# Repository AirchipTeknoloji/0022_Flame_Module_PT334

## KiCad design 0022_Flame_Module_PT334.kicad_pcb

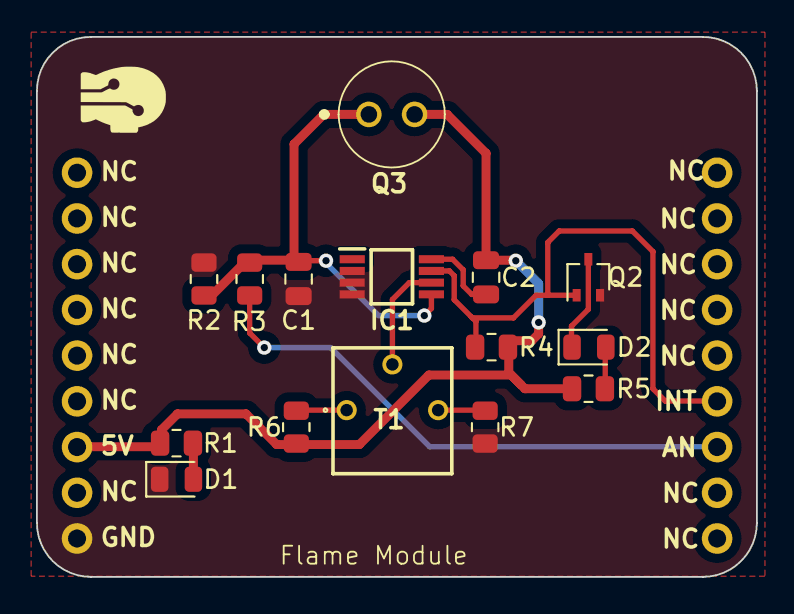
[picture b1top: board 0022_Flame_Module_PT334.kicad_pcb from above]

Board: 2 copper layers, 40.0 x 30.0 mm, 16 parts (0 on the bottom side), 10 nets.

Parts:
C1: 10nF; C_0805_2012Metric
C2: 2.2uF; C_0805_2012Metric
D1, D2: LED; LED_0805_2012Metric
IC1: LM2903BHQDGKRQ1; SOP65P490X110-8N
Q2: PDTC114EU,115; SOT-323_SC-70
Q3: PT334-6B; PT3346B
R1: 1k; R_0805_2012Metric
R2: 6k8; R_0805_2012Metric
R3: 3k3; R_0805_2012Metric
R4, R5: 4k7; R_0805_2012Metric
R6, R7: 5k1; R_0805_2012Metric
T1: R_Potentiometer_Trim; 3362P_1
U2: air_module

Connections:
+5V: C2.1, Q3.2 (C), R1.1, R4.1, R5.1, R6.1, U2.7 (5V)
AN: R3.1, U2.12 (GPIO)
GND: C1.2, D1.1 (K), IC1.2 (1IN-), IC1.3 (1IN+), IC1.4 (GND), Q2.2 (E), R2.2, R7.2, U2.9 (GND)
IN+: C1.1, IC1.5 (2IN+), Q3.1 (E), R2.1, R3.2
IN-: IC1.6 (2IN-), T1.2
INT: IC1.7 (2OUT), Q2.1 (B), R4.2, U2.13 (GPIO)
unnamed: D1.2 (A), R1.2
unnamed: D2.2 (A), R5.2
unnamed: D2.1 (K), Q2.3 (C)
unnamed: C2.2, IC1.8 (VCC)
